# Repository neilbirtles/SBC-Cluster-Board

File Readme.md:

# SBC Cluster Board

## Overview

From many years of building Single Board Computer (SBC) Clusters and the pain to all the cables and configuration that goes with it came the idea to make a cluster board that didn't need lots of cables or a separate network switch to make it function. The SBC Cluster (SBC&#178;) Board is the embodiment of that idea.

The SBC&#178;Board will allow 5 SBC to be powered and networked over their USB-C connection. The SBC&#178; can provide up to 3.2A per port, with adjustable current limits to help limit damage in the event of any failures on the SBC themselves. Networking is provided through the use of USB gadget mode ethernet drivers that are standard in most Linux kernels.

Optional monitoring of the state of the SBC&#178; is achieved over an I2C connection to a host device. Configuration of the board is also possible over this link. A web frontend has been developed to make this a simple process without having to send arcane commands to specific registers on the I2C devices on the SBC&#178;.

The slots for SBC have been spaced so that a single 120mm fan can cool them all removing the noise of 5 smaller fans. The SBC&#178; provides a 12V step-up converter to power the fans from the proper voltage to ensure efficient cooling without the need for a second power supply.

A single 5v 100W power supply (e.g. LRS-100-5) is all that is needed to comfortably run 5 SBC meaning that the only cables required for the complete cluster are 1 mains cable to the power supply, 2 wires for +5v and 0V DC to the SBC&#178; and an optional 3 way cable to provide I2C comms back to a host device.

## SBC&#178; Components

There are a number of folders in this repository for the different components that make up the SBC&#178;. They are as follows:

##### PCB

This folder contains all the design files for the PCB, along with manufacturing information

##### Firmware

This folder contains the firmware that is flashed to the two microcontrollers that provide the control and monitoring functionality on the SBC&#178;

##### Frontend

This folder contains a Flask and Bootstrap based web frontend that can be run on one of the SBC in the cluster to provide information about and control over the SBC&#178;

##### Cases and Accessories

This folder contains the designs for the cases and accessories related to the SBC&#178;.

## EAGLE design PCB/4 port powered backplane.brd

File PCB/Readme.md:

# PCB Information

This is the PCB for the 5 way SBC Cluster Board. It has been produced in Eagle PCB.

## Manufacture Information

The PCBs have all been made by JLCPCB (https://jlcpcb.com/). The boards are 4 layer and must be made using controlled impedance due to the USB differential traces. The boards must be made 1.6mm thick and with the JLC controlled impedance process JLC7628

## Board Configuration

### Mains Power Measurement

There is provision on the board to use a current sensor IC to determine mains power usage for the system - this feature is mainly aimed at use in crypto currency applications where it is useful to know power consumption for the system to allow profitability to be calculated. If this function is not required then Resistor R44 is fitted to signal to the microcontroller that this function is not present on the board and J10, J11, IC7, C21 and C24 are not fitted.

### 12V DC Step-Up

The board also provides the ability to step up the incoming 5V supply to 12V to allow a standard PC fan to be powered without needing an additional power supply. The fan is connected via J8 and is the standard PC fan pinout. There is no speed control of the fan provided. If this is not required then components J8, D1, D2, C22, C23, R38, R39, IC8 and L1 are not fitted.

### Notes

IC5 can not be socketed otherwise it will foul the SBC plugged into J4. It must therefore be programmed and then soldered in

JP2 and JP3 are the programming headers for the microcontrollers on the board - they do not have to be fitted if pogo pins or similar are used to make contact for programming. Note that these headers are also used in the initial calibration (see firmware information) but the pads can be easily held low without the header fitted. 

JP4 provides the I2C bus out from the board and is set up to be a 3.3v bus with the relevant pull up resistors fitted to the board at R17 and R18 - these can be left off if the interfacing device already has pull up resistors in place. The pin-out for this is indicated on the PCB silk screen as 0-D-C for 0v, Data and Clock.

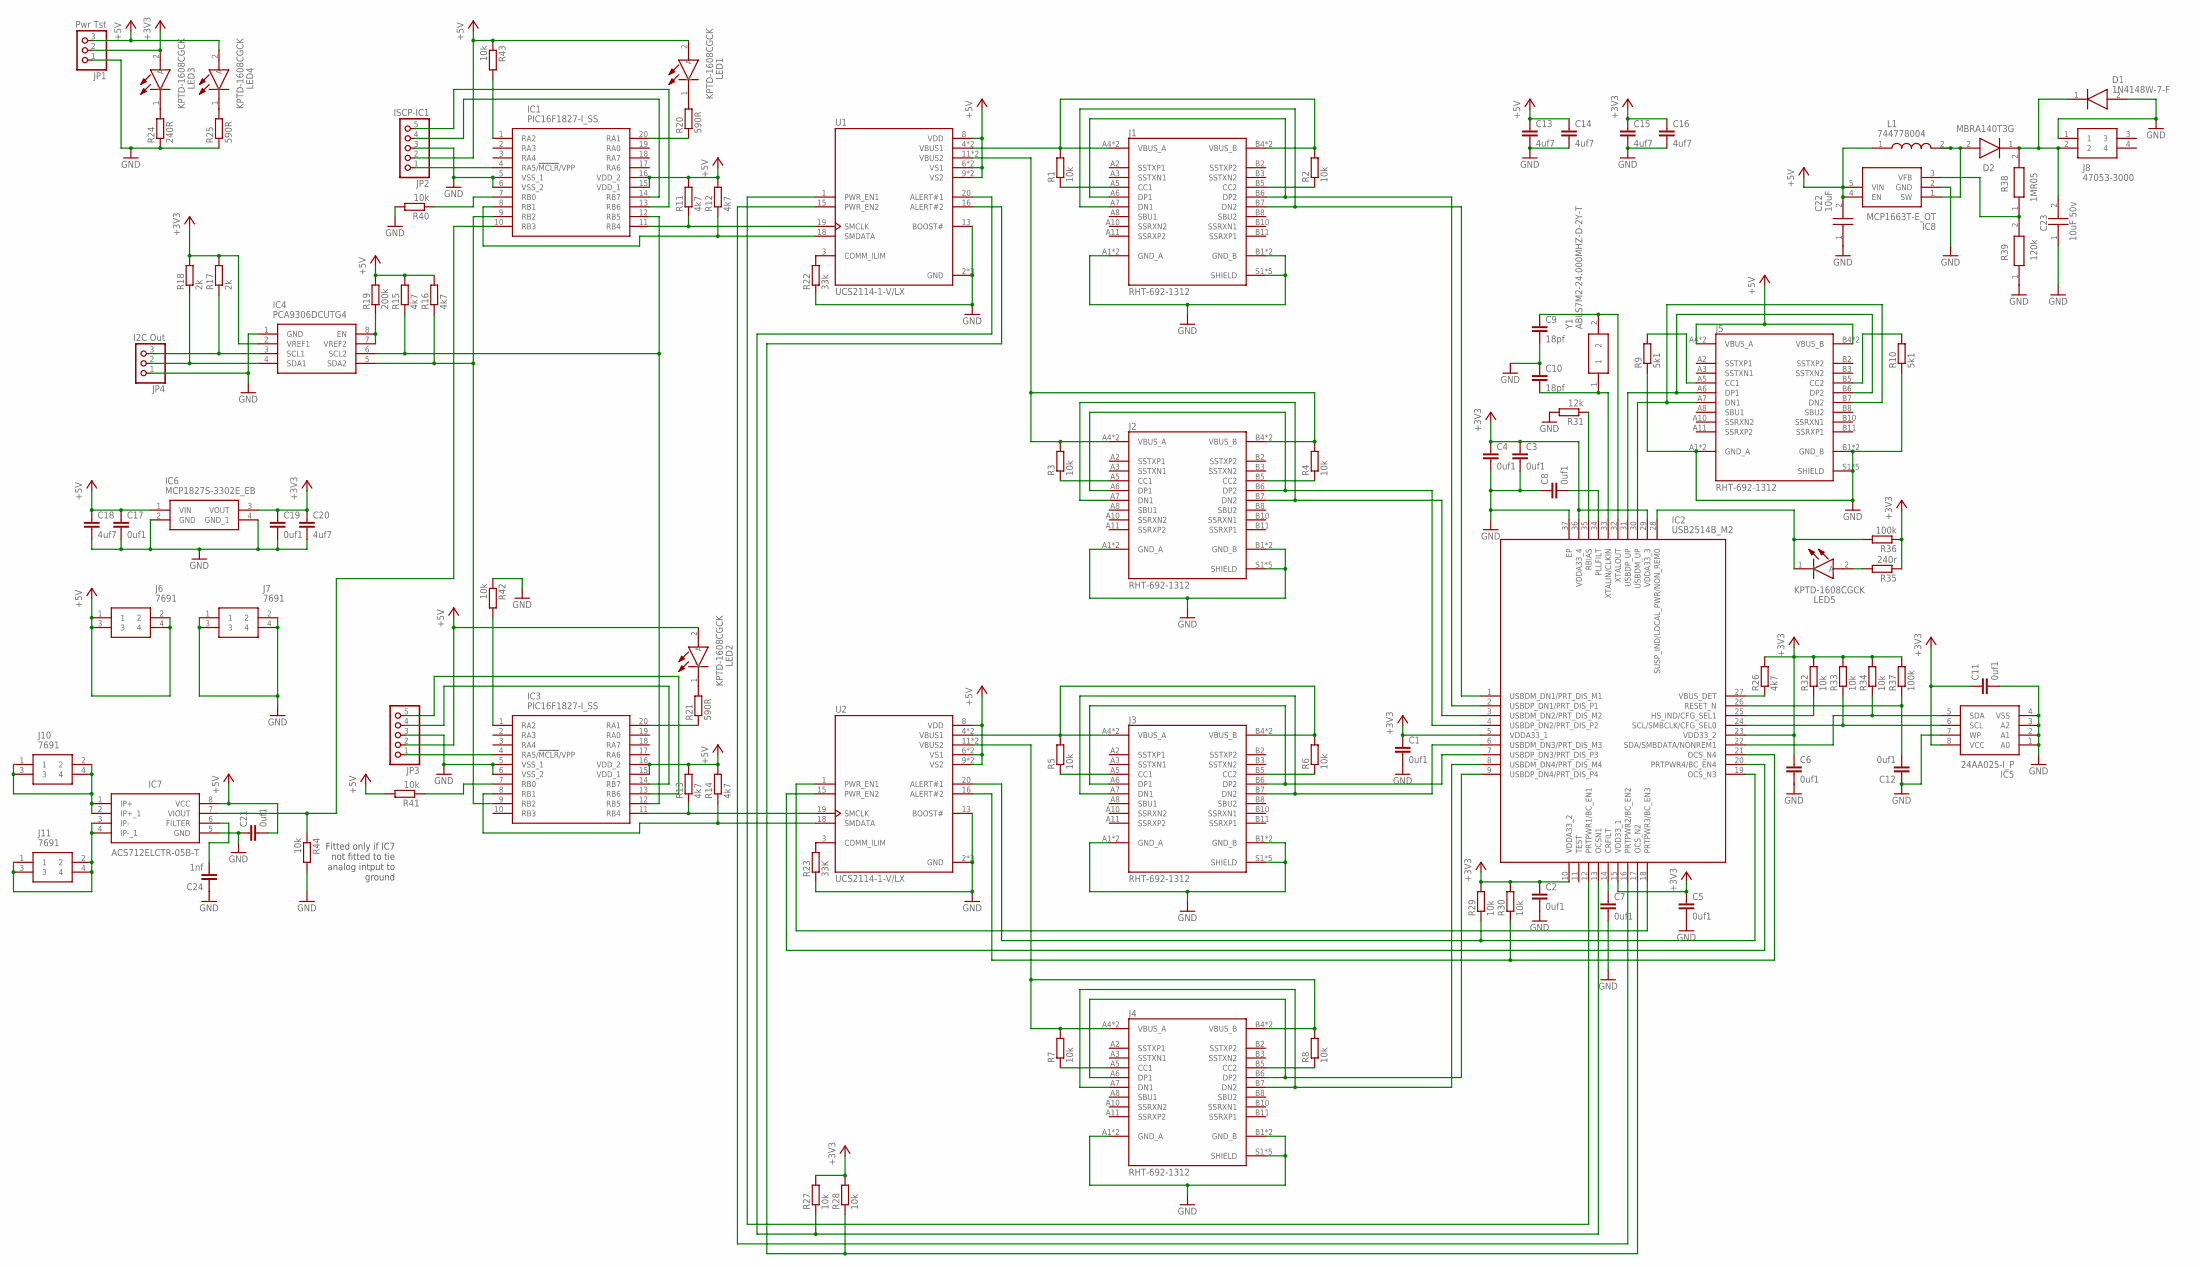
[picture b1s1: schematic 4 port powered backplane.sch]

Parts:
C1, C2, C3, C4, C5, C6, C7, C8, C11, C12, C17, C19, C21: 0uf1; C0603
C9, C10: 18pf; C0603
C13, C14, C15, C16, C18, C20: 4uf7; C0603
C22: 10uF; CAPC2012X145N
C23: 10uF 50v; CAPC3225X230N
C24: 1nf; C0603
D1: 1N4148W-7-F; SOD3716X115N
D2: MBRA140T3G; DIOM5226X220N
IC1, IC3: PIC16F1827-I_SS; SOP65P780X200-20N
IC2: USB2514B_M2; QFN50P600X600X100-37N
IC4: PCA9306DCUTG4; SOP50P310X90-8N
IC5: 24AA025-I_P; DIP781W56P254L950H533Q8N
IC6: MCP1827S-3302E_EB; TO254P1491X508-4N
IC7: ACS712ELCTR-05B-T; SOIC127P600X175-8N
IC8: MCP1663T-E_OT; SOT95P270X145-5N
J1, J2, J3, J4, J5: RHT-692-1312; RENHOTEC_RHT-692-1312
J6, J7, J10, J11: 7691
J8: 47053-3000; 470533000
JP1: Pwr Tst; 1X03
JP2: ISCP-IC1; 1X05
JP3: PINHD-1X5; 1X05
JP4: I2C Out; 1X03
L1: 744778004
LED1, LED2, LED3, LED4, LED5: KPTD-1608CGCK; LEDC1608X85N
R1, R2, R3, R4, R5, R6, R7, R8, R27, R28, R29, R30, R32, R33, R34, R40, R41, R42, R43, R44: 10k; R0603
R9, R10: 5k1; R0603
R11, R12, R13, R14, R15, R16, R26: 4k7; R0603
R17, R18: 2k; R0603
R19: 200k; R0603
R20, R21, R25: 590R; R0603
R22: 33k; R0603
R23: 33K; R0603
R24: 240R; R0603
R31: 12k; R0603
R35: 240r; R0603
R36, R37: 100k; R0603
R38: 1MR05; RESC2012X70N
R39: 120k; RESC2012X70N
U1, U2: UCS2114-1-V/LX; IC_UCS2114-1-V/LX
Y1: ABLS7M2-24.000MHZ-D-2Y-T; ABLS7M2

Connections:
+3V3: C1.1, C2.1, C3.1, C4.1, C5.1, C6.1, C11.1, C15.1, C16.1, C19.1, C20.1, IC2.5 (VDDA33_1), IC2.10 (VDDA33_2), IC2.15 (VDD33_1), IC2.23 (VDD33_2), IC2.29 (VDDA33_3), IC2.36 (VDDA33_4), IC4.2 (VREF1), IC5.8 (VCC), IC6.3 (VOUT), JP1.2, LED3.2 (A), R17.2, R18.2, R26.2, R27.2, R28.2, R29.2, R30.2, R32.2, R33.2, R34.2, R35.1, R36.1, R37.2
+5V: C13.1, C14.1, C17.1, C18.1, C21.2, C22.2, IC1.15 (VDD_1), IC1.16 (VDD_2), IC3.15 (VDD_1), IC3.16 (VDD_2), IC6.1 (VIN), IC7.8 (VCC), IC8.4 (EN), IC8.5 (VIN), J5.A4 (VBUS_A), J5.A9 (VBUS_A), J5.B4 (VBUS_B), J5.B9 (VBUS_B), J6.1, J6.2, J6.3, J6.4, JP1.3, JP2.2, JP3.2, L1.1, LED1.2 (A), LED2.2 (A), LED4.2 (A), R11.2, R12.2, R13.2, R14.2, R15.2, R16.2, R19.2, R41.2, R43.1, U1.6 (VS1), U1.7 (VS1), U1.8 (VDD), U1.9 (VS2), U1.10 (VS2), U2.6 (VS1), U2.7 (VS1), U2.8 (VDD), U2.9 (VS2), U2.10 (VS2)
DOWN1_N: IC2.1 (USBDM_DN1/PRT_DIS_M1), J1.A7 (DN1), J1.B7 (DN2)
DOWN1_P: IC2.2 (USBDP_DN1/PRT_DIS_P1), J1.A6 (DP1), J1.B6 (DP2)
DOWN2_N: IC2.3 (USBDM_DN2/PRT_DIS_M2), J2.A7 (DN1), J2.B7 (DN2)
DOWN2_P: IC2.4 (USBDP_DN2/PRT_DIS_P2), J2.A6 (DP1), J2.B6 (DP2)
DOWN3_N: IC2.6 (USBDM_DN3/PRT_DIS_M3), J3.A7 (DN1), J3.B7 (DN2)
DOWN3_P: IC2.7 (USBDP_DN3/PRT_DIS_P3), J3.A6 (DP1), J3.B6 (DP2)
DOWN4_N: IC2.8 (USBDM_DN4/PRT_DIS_M4), J4.A7 (DN1), J4.B7 (DN2)
DOWN4_P: IC2.9 (USBDP_DN4/PRT_DIS_P4), J4.A6 (DP1), J4.B6 (DP2)
GND: C1.2, C2.2, C3.2, C4.2, C5.2, C6.2, C7.2, C8.1, C9.2, C10.1, C11.2, C12.1, C13.2, C14.2, C15.2, C16.2, C17.2, C18.2, C19.2, C20.2, C21.1, C22.1, C23.1, C24.1, D1.2 (A), IC1.5 (VSS_1), IC1.6 (VSS_2), IC2.37 (EP), IC3.5 (VSS_1), IC3.6 (VSS_2), IC4.1 (GND), IC5.1 (A0), IC5.2 (A1), IC5.3 (A2), IC5.4 (VSS), IC5.7 (WP), IC6.2 (GND), IC6.4 (GND_1), IC7.5 (GND), IC8.2 (GND), J1.A1 (GND_A), J1.A12 (GND_A), J1.B1 (GND_B), J1.B12 (GND_B), J1.S1 (SHIELD), J1.S2 (SHIELD), J1.S3 (SHIELD), J1.S4 (SHIELD), J1.S5 (SHIELD), J2.A1 (GND_A), J2.A12 (GND_A), J2.B1 (GND_B), J2.B12 (GND_B), J2.S1 (SHIELD), J2.S2 (SHIELD), J2.S3 (SHIELD), J2.S4 (SHIELD), J2.S5 (SHIELD), J3.A1 (GND_A), J3.A12 (GND_A), J3.B1 (GND_B), J3.B12 (GND_B), J3.S1 (SHIELD), J3.S2 (SHIELD), J3.S3 (SHIELD), J3.S4 (SHIELD), J3.S5 (SHIELD), J4.A1 (GND_A), J4.A12 (GND_A), J4.B1 (GND_B), J4.B12 (GND_B), J4.S1 (SHIELD), J4.S2 (SHIELD), J4.S3 (SHIELD), J4.S4 (SHIELD), J4.S5 (SHIELD), J5.A1 (GND_A), J5.A12 (GND_A), J5.B1 (GND_B), J5.B12 (GND_B), J5.S1 (SHIELD), J5.S2 (SHIELD), J5.S3 (SHIELD), J5.S4 (SHIELD), J5.S5 (SHIELD), J7.1, J7.2, J7.3, J7.4, J8.1, JP1.1, JP2.3, JP3.3, JP4.1, R9.1, R10.1, R22.1, R23.1, R24.1, R25.1, R31.2, R39.1, R40.2, R42.1, R44.2, U1.2 (GND), U1.13 (BOOST#), U1.14 (GND), U1.17 (GND), U2.2 (GND), U2.13 (BOOST#), U2.14 (GND), U2.17 (GND)
unnamed: IC1.10 (RB3), IC7.7 (VIOUT), R44.1
unnamed: D2.2 (A), IC8.1 (SW), L1.2
unnamed: C23.2, D1.1 (K), D2.1 (K), J8.2, R38.2
unnamed: IC8.3 (VFB), R38.1, R39.2
unnamed: C24.2, IC7.6 (FILTER)
unnamed: IC1.7 (RB0), R40.1
unnamed: IC3.7 (RB0), R41.1
unnamed: IC3.1 (RA2), R42.2
unnamed: IC1.1 (RA2), R43.2
unnamed: J5.A5 (CC1), R9.2
unnamed: J5.B5 (CC2), R10.2
unnamed: IC1.11 (RB4), R11.1, U1.19 (SMCLK)
unnamed: IC2.27 (VBUS_DET), R26.1
unnamed: J2.A5 (CC1), R3.1
unnamed: J2.B5 (CC2), R4.1
unnamed: J1.A5 (CC1), R1.1
unnamed: J1.B5 (CC2), R2.1
unnamed: J4.A5 (CC1), R7.1
unnamed: J4.B5 (CC2), R8.1
unnamed: J1.A4 (VBUS_A), J1.A9 (VBUS_A), J1.B4 (VBUS_B), J1.B9 (VBUS_B), R1.2, R2.2, U1.4 (VBUS1), U1.5 (VBUS1)
unnamed: J2.A4 (VBUS_A), J2.A9 (VBUS_A), J2.B4 (VBUS_B), J2.B9 (VBUS_B), R3.2, R4.2, U1.11 (VBUS2), U1.12 (VBUS2)
unnamed: J3.A5 (CC1), R5.1
unnamed: J3.B5 (CC2), R6.1
unnamed: IC2.13 (OCSN1), R27.1, U1.20 (ALERT#1)
unnamed: IC2.12 (PRTPWR1/BC_EN1), U1.1 (PWR_EN1)
unnamed: IC2.16 (PRTPWR2/BC_EN2), U1.15 (PWR_EN2)
unnamed: IC2.17 (OCS_N2), R28.1, U1.16 (ALERT#2)
unnamed: IC2.18 (PRTPWR3/BC_EN3), U2.1 (PWR_EN1)
unnamed: IC2.20 (PRTPWR4/BC_EN4), U2.15 (PWR_EN2)
unnamed: IC2.19 (OCS_N3), R29.1, U2.20 (ALERT#1)
unnamed: IC2.21 (OCS_N4), R30.1, U2.16 (ALERT#2)
unnamed: IC3.11 (RB4), R13.1, U2.19 (SMCLK)
unnamed: IC3.8 (RB1), R14.1, U2.18 (SMDATA)
unnamed: IC1.9 (RB2), IC3.9 (RB2), IC4.5 (SDA2), R16.1
unnamed: IC1.12 (RB5), IC3.12 (RB5), IC4.6 (SCL2), R15.1
unnamed: C7.1, IC2.14 (CRFILT)
unnamed: IC1.8 (RB1), R12.1, U1.18 (SMDATA)
unnamed: IC1.4 (RA5/!MCLR!/VPP), JP2.1
unnamed: IC4.7 (VREF2), IC4.8 (EN), R19.1
unnamed: IC4.3 (SCL1), JP4.3, R17.1
unnamed: IC4.4 (SDA1), JP4.2, R18.1
unnamed: IC3.4 (RA5/!MCLR!/VPP), JP3.1
unnamed: IC1.14 (RB7), JP2.4
unnamed: IC1.13 (RB6), JP2.5
unnamed: IC3.14 (RB7), JP3.4
unnamed: IC3.13 (RB6), JP3.5
unnamed: IC1.20 (RA1), R20.1
unnamed: IC3.20 (RA1), R21.1
unnamed: LED1.1 (K), R20.2
unnamed: LED2.1 (K), R21.2
unnamed: R22.2, U1.3 (COMM_ILIM)
unnamed: R23.2, U2.3 (COMM_ILIM)
unnamed: LED3.1 (K), R24.2
unnamed: LED4.1 (K), R25.2
unnamed: C8.2, IC2.34 (PLLFILT)
unnamed: C10.2, IC2.33 (XTALIN/CLKIN), Y1.1
unnamed: C9.1, IC2.32 (XTALOUT), Y1.2
unnamed: IC2.24 (SCL/SMBCLK/CFG_SEL0), IC5.6 (SCL), R33.1
unnamed: IC2.22 (SDA/SMBDATA/NONREM1), IC5.5 (SDA), R34.1
unnamed: IC2.35 (RBIAS), R31.1
unnamed: IC2.25 (HS_IND/CFG_SEL1), R32.1
unnamed: LED5.2 (A), R35.2
unnamed: IC2.28 (SUSP_IND/LOCAL_PWR/NON_REM0), LED5.1 (K), R36.2
unnamed: C12.2, IC2.26 (RESET_N), R37.1
unnamed: IC7.3 (IP-), IC7.4 (IP-_1), J11.1, J11.2, J11.3, J11.4
unnamed: IC7.1 (IP+), IC7.2 (IP+_1), J10.1, J10.2, J10.3, J10.4
PWR3: J3.A4 (VBUS_A), J3.A9 (VBUS_A), J3.B4 (VBUS_B), J3.B9 (VBUS_B), R5.2, R6.2, U2.4 (VBUS1), U2.5 (VBUS1)
PWR4: J4.A4 (VBUS_A), J4.A9 (VBUS_A), J4.B4 (VBUS_B), J4.B9 (VBUS_B), R7.2, R8.2, U2.11 (VBUS2), U2.12 (VBUS2)
UP_N: IC2.30 (USBDM_UP), J5.A7 (DN1), J5.B7 (DN2)
UP_P: IC2.31 (USBDP_UP), J5.A6 (DP1), J5.B6 (DP2)

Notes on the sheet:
Fitted only if IC7 not fitted to tie analog intput to ground

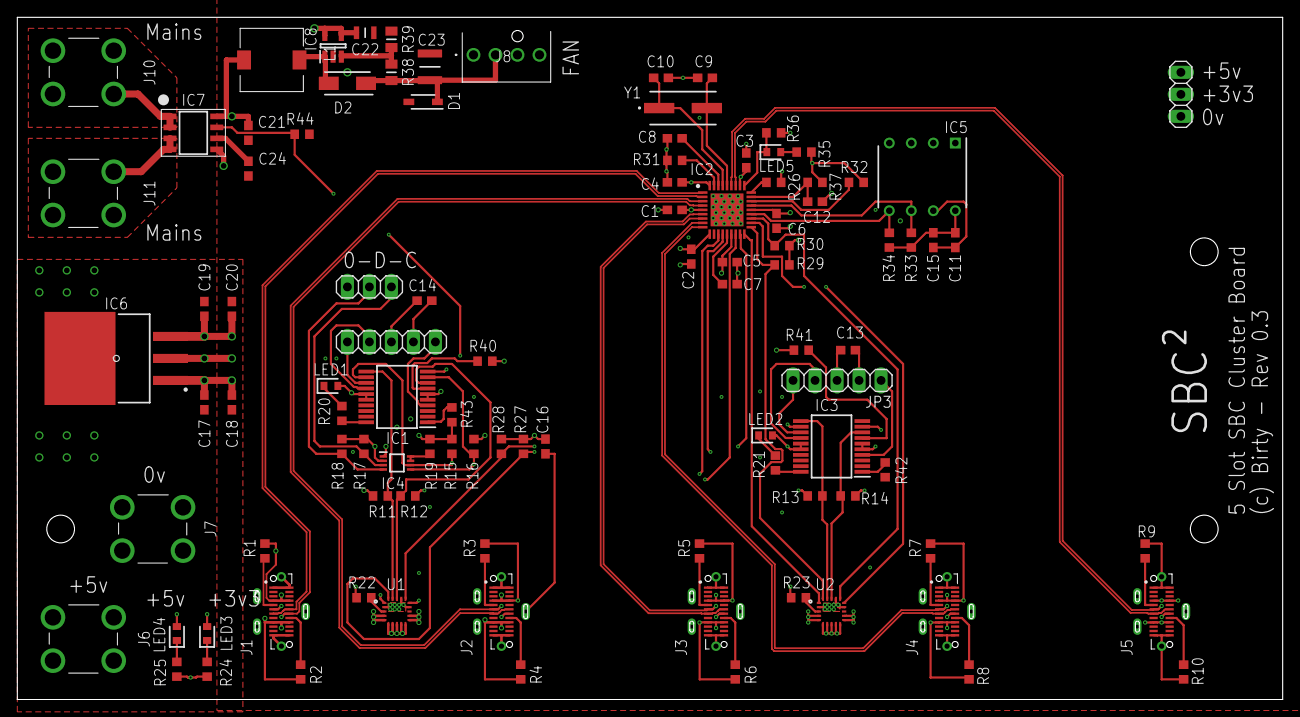
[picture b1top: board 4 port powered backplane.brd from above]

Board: 4 copper layers, 146.0 x 78.7 mm, 101 parts (0 on the bottom side), 81 nets.

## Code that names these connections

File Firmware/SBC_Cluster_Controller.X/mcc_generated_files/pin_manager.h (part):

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// get/set LED aliases
#define LED_TRIS                 TRISAbits.TRISA1
#define LED_LAT                  LATAbits.LATA1
#define LED_PORT                 PORTAbits.RA1
#define LED_ANS                  ANSELAbits.ANSA1
#define LED_SetHigh()            do { LATAbits.LATA1 = 1; } while(0)
#define LED_SetLow()             do { LATAbits.LATA1 = 0; } while(0)
#define LED_Toggle()             do { LATAbits.LATA1 = ~LATAbits.LATA1; } while(0)
#define LED_GetValue()           PORTAbits.RA1
#define LED_SetDigitalInput()    do { TRISAbits.TRISA1 = 1; } while(0)
#define LED_SetDigitalOutput()   do { TRISAbits.TRISA1 = 0; } while(0)
#define LED_SetAnalogMode()      do { ANSELAbits.ANSA1 = 1; } while(0)
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// get/set Has_Mains_Current_Sensor aliases
#define Has_Mains_Current_Sensor_TRIS                 TRISAbits.TRISA2
#define Has_Mains_Current_Sensor_LAT                  LATAbits.LATA2
#define Has_Mains_Current_Sensor_PORT                 PORTAbits.RA2
#define Has_Mains_Current_Sensor_ANS                  ANSELAbits.ANSA2
#define Has_Mains_Current_Sensor_SetHigh()            do { LATAbits.LATA2 = 1; } while(0)
#define Has_Mains_Current_Sensor_SetLow()             do { LATAbits.LATA2 = 0; } while(0)
#define Has_Mains_Current_Sensor_Toggle()             do { LATAbits.LATA2 = ~LATAbits.LATA2; } while(0)
#define Has_Mains_Current_Sensor_GetValue()           PORTAbits.RA2
#define Has_Mains_Current_Sensor_SetDigitalInput()    do { TRISAbits.TRISA2 = 1; } while(0)
#define Has_Mains_Current_Sensor_SetDigitalOutput()   do { TRISAbits.TRISA2 = 0; } while(0)
#define Has_Mains_Current_Sensor_SetAnalogMode()      do { ANSELAbits.ANSA2 = 1; } while(0)
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// get/set I2C_Addr_Bit aliases
#define I2C_Addr_Bit_TRIS                 TRISBbits.TRISB0
#define I2C_Addr_Bit_LAT                  LATBbits.LATB0
#define I2C_Addr_Bit_PORT                 PORTBbits.RB0
#define I2C_Addr_Bit_WPU                  WPUBbits.WPUB0
#define I2C_Addr_Bit_SetHigh()            do { LATBbits.LATB0 = 1; } while(0)
#define I2C_Addr_Bit_SetLow()             do { LATBbits.LATB0 = 0; } while(0)
#define I2C_Addr_Bit_Toggle()             do { LATBbits.LATB0 = ~LATBbits.LATB0; } while(0)
#define I2C_Addr_Bit_GetValue()           PORTBbits.RB0
#define I2C_Addr_Bit_SetDigitalInput()    do { TRISBbits.TRISB0 = 1; } while(0)
#define I2C_Addr_Bit_SetDigitalOutput()   do { TRISBbits.TRISB0 = 0; } while(0)
#define I2C_Addr_Bit_SetPullup()          do { WPUBbits.WPUB0 = 1; } while(0)
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#define RB1_SetHigh()            do { LATBbits.LATB1 = 1; } while(0)
#define RB1_SetLow()             do { LATBbits.LATB1 = 0; } while(0)
#define RB1_Toggle()             do { LATBbits.LATB1 = ~LATBbits.LATB1; } while(0)
#define RB1_GetValue()              PORTBbits.RB1
#define RB1_SetDigitalInput()    do { TRISBbits.TRISB1 = 1; } while(0)
#define RB1_SetDigitalOutput()   do { TRISBbits.TRISB1 = 0; } while(0)
#define RB1_SetPullup()             do { WPUBbits.WPUB1 = 1; } while(0)
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#define RB2_SetHigh()            do { LATBbits.LATB2 = 1; } while(0)
#define RB2_SetLow()             do { LATBbits.LATB2 = 0; } while(0)
#define RB2_Toggle()             do { LATBbits.LATB2 = ~LATBbits.LATB2; } while(0)
#define RB2_GetValue()              PORTBbits.RB2
#define RB2_SetDigitalInput()    do { TRISBbits.TRISB2 = 1; } while(0)
#define RB2_SetDigitalOutput()   do { TRISBbits.TRISB2 = 0; } while(0)
#define RB2_SetPullup()             do { WPUBbits.WPUB2 = 1; } while(0)
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// get/set Mains_Current_Sensor aliases
#define Mains_Current_Sensor_TRIS                 TRISBbits.TRISB3
#define Mains_Current_Sensor_LAT                  LATBbits.LATB3
#define Mains_Current_Sensor_PORT                 PORTBbits.RB3
#define Mains_Current_Sensor_WPU                  WPUBbits.WPUB3
#define Mains_Current_Sensor_ANS                  ANSELBbits.ANSB3
#define Mains_Current_Sensor_SetHigh()            do { LATBbits.LATB3 = 1; } while(0)
#define Mains_Current_Sensor_SetLow()             do { LATBbits.LATB3 = 0; } while(0)
#define Mains_Current_Sensor_Toggle()             do { LATBbits.LATB3 = ~LATBbits.LATB3; } while(0)
#define Mains_Current_Sensor_GetValue()           PORTBbits.RB3
#define Mains_Current_Sensor_SetDigitalInput()    do { TRISBbits.TRISB3 = 1; } while(0)
#define Mains_Current_Sensor_SetDigitalOutput()   do { TRISBbits.TRISB3 = 0; } while(0)
#define Mains_Current_Sensor_SetPullup()          do { WPUBbits.WPUB3 = 1; } while(0)
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#define RB4_SetHigh()            do { LATBbits.LATB4 = 1; } while(0)
#define RB4_SetLow()             do { LATBbits.LATB4 = 0; } while(0)
#define RB4_Toggle()             do { LATBbits.LATB4 = ~LATBbits.LATB4; } while(0)
#define RB4_GetValue()              PORTBbits.RB4
#define RB4_SetDigitalInput()    do { TRISBbits.TRISB4 = 1; } while(0)
#define RB4_SetDigitalOutput()   do { TRISBbits.TRISB4 = 0; } while(0)
#define RB4_SetPullup()             do { WPUBbits.WPUB4 = 1; } while(0)
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#define RB5_SetHigh()            do { LATBbits.LATB5 = 1; } while(0)
#define RB5_SetLow()             do { LATBbits.LATB5 = 0; } while(0)
#define RB5_Toggle()             do { LATBbits.LATB5 = ~LATBbits.LATB5; } while(0)
#define RB5_GetValue()              PORTBbits.RB5
#define RB5_SetDigitalInput()    do { TRISBbits.TRISB5 = 1; } while(0)
#define RB5_SetDigitalOutput()   do { TRISBbits.TRISB5 = 0; } while(0)
#define RB5_SetPullup()             do { WPUBbits.WPUB5 = 1; } while(0)
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// get/set Start_Voltage_Cal aliases
#define Start_Voltage_Cal_TRIS                 TRISBbits.TRISB6
#define Start_Voltage_Cal_LAT                  LATBbits.LATB6
#define Start_Voltage_Cal_PORT                 PORTBbits.RB6
#define Start_Voltage_Cal_WPU                  WPUBbits.WPUB6
#define Start_Voltage_Cal_ANS                  ANSELBbits.ANSB6
#define Start_Voltage_Cal_SetHigh()            do { LATBbits.LATB6 = 1; } while(0)
#define Start_Voltage_Cal_SetLow()             do { LATBbits.LATB6 = 0; } while(0)
#define Start_Voltage_Cal_Toggle()             do { LATBbits.LATB6 = ~LATBbits.LATB6; } while(0)
#define Start_Voltage_Cal_GetValue()           PORTBbits.RB6
#define Start_Voltage_Cal_SetDigitalInput()    do { TRISBbits.TRISB6 = 1; } while(0)
#define Start_Voltage_Cal_SetDigitalOutput()   do { TRISBbits.TRISB6 = 0; } while(0)
#define Start_Voltage_Cal_SetPullup()          do { WPUBbits.WPUB6 = 1; } while(0)
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// get/set Enter_Voltage_Cal aliases
#define Enter_Voltage_Cal_TRIS                 TRISBbits.TRISB7
#define Enter_Voltage_Cal_LAT                  LATBbits.LATB7
#define Enter_Voltage_Cal_PORT                 PORTBbits.RB7
#define Enter_Voltage_Cal_WPU                  WPUBbits.WPUB7
#define Enter_Voltage_Cal_ANS                  ANSELBbits.ANSB7
#define Enter_Voltage_Cal_SetHigh()            do { LATBbits.LATB7 = 1; } while(0)
#define Enter_Voltage_Cal_SetLow()             do { LATBbits.LATB7 = 0; } while(0)
#define Enter_Voltage_Cal_Toggle()             do { LATBbits.LATB7 = ~LATBbits.LATB7; } while(0)
#define Enter_Voltage_Cal_GetValue()           PORTBbits.RB7
#define Enter_Voltage_Cal_SetDigitalInput()    do { TRISBbits.TRISB7 = 1; } while(0)
#define Enter_Voltage_Cal_SetDigitalOutput()   do { TRISBbits.TRISB7 = 0; } while(0)
#define Enter_Voltage_Cal_SetPullup()          do { WPUBbits.WPUB7 = 1; } while(0)
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
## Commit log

2020-07-19 Initial open sourcing of SBC²
2020-07-19 Fixed markdown in readmes
2020-10-27 Set code offset to 0x300 and set mem model for use with bootloader
    tweaks:
    updated readme to reflect offset
    Fixed project name from development
    Removed MPLab files not needed in gitignore and kept the built hexfile
2020-10-27 Initial frontend
    power monitoring working
2020-10-28 Added ability to hard reset each slot
    fixed slot 2 displaying slot 1 current
2020-10-28 Frimware update backend code
2020-11-03 Firmware flashing working
2020-11-08 Fixed firmware update; Fixed occasional conflict between bootloader and program I2C comms
2020-12-13 Added case designs
2021-01-20 removed errant wiringpi in requirements.txt
2021-03-20 Bump jinja2 from 2.11.2 to 2.11.3 in /Frontend
    Bumps [jinja2](https://github.com/pallets/jinja) from 2.11.2 to 2.11.3.
    - [Release notes](https://github.com/pallets/jinja/releases)
    - [Changelog](https://github.com/pallets/jinja/blob/master/CHANGES.rst)
    - [Commits](https://github.com/pallets/jinja/compare/2.11.2...2.11.3)

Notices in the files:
Firmware/SBC_Cluster_Controller.X/mcc_generated_files/pin_manager.h:
(c) 2018 Microchip Technology Inc. and its subsidiaries.
